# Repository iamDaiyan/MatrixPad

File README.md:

# MatrixPad
A 9 Key Programmable Macropad with Encoder & OLED Display<br><br>
MatrixPad is a fully programmable 9-key macropad designed for productivity, content creation, coding, and everyday shortcuts. Built around the **Seeed XIAO RP2040**, it features 9 Mechanical keys, a clean 3D-printed enclosure, rotary encoder input, and OLED display support.
## Features
* 9 Mechanical Keys (3x3 grid layout)
* Rotary Encoder 
* 0.91 inch OLED Display 
* Powered by Seeed XIAO RP2040 (Through-Hole)
* 2-Layer PCB (≤100mm x 100mm)
* Fully 3D Printed Case
* Programmable Firmware (KMK / QMK compatible)

---

## Overall Hackpad

## Schematic

## PCB

## Case Design

---

## BOM

| Item                          | Quantity |
|-------------------------------|----------|
| Seeed XIAO RP2040 (Through-Hole) | 1        |
| MX-Style Mechanical Switches  | 9        |
| Through-hole 1N4148 Diodes    | 9        |
| Blank DSA Keycaps (1u)        | 9        |
| SK6812 MINI-E LEDs             | 9        |
| EC11 Rotary Encoder            | 1        |
| 0.91” OLED (I2C)              | 1        |
| M3×16 mm Screws                | 4        |
| M3×5 mm Heatset Inserts        | 4        |
| PCB (2-Layer)                  | 1        |
| 3D Printed Case                | 1        |

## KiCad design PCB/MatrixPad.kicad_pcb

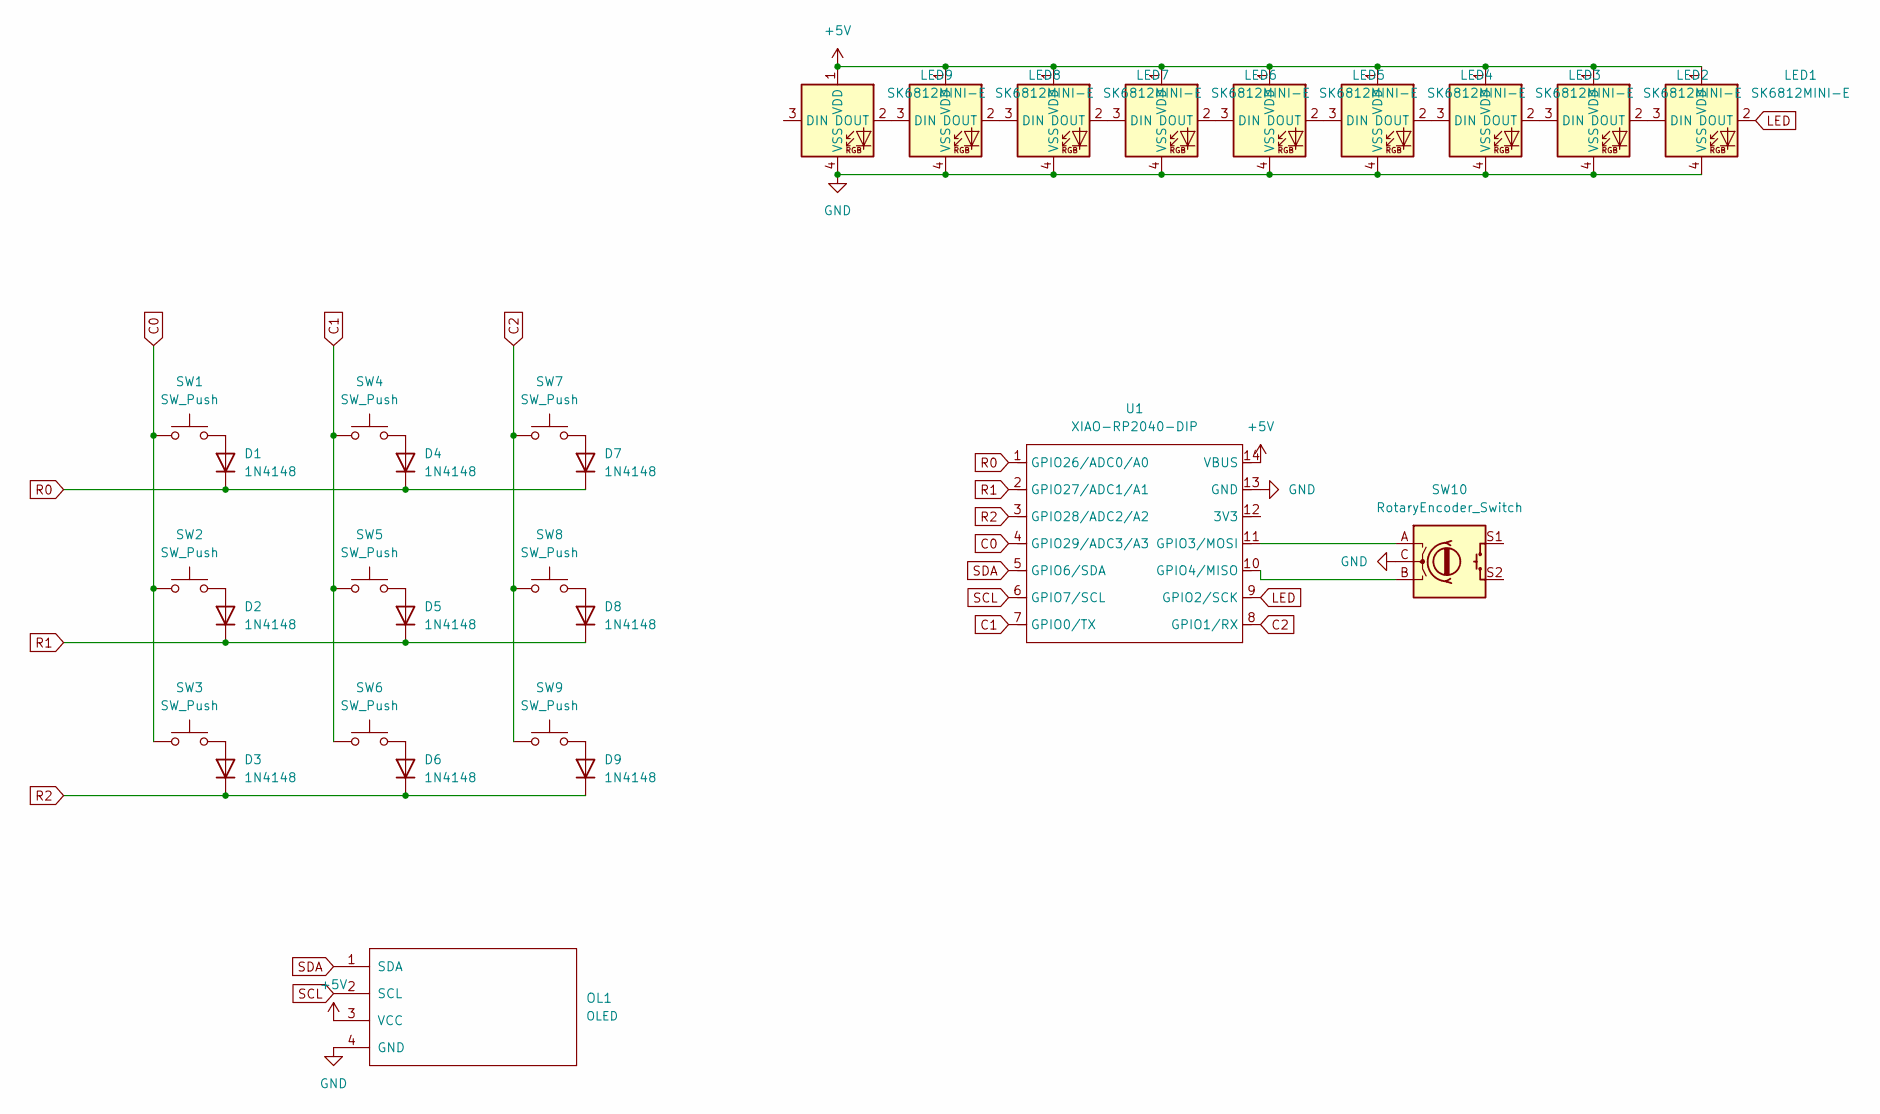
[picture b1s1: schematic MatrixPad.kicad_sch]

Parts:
D1, D2, D3, D4, D5, D6, D7, D8, D9: 1N4148; D_DO-35_SOD27_P7.62mm_Horizontal
LED1, LED2, LED3, LED4, LED5, LED6, LED7, LED8, LED9: SK6812MINI-E; LED_6028R
OL1: OLED; Adafruit_SSD1306
SW1, SW2, SW3, SW4, SW5, SW6, SW7, SW8, SW9: SW_Push; SW_Cherry_MX_1.00u_PCB
SW10: RotaryEncoder_Switch; RotaryEncoder_Alps_EC11E-Switch_Vertical_H20mm
U1: XIAO-RP2040-DIP

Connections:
+5V: LED1.1 (VDD), LED2.1 (VDD), LED3.1 (VDD), LED4.1 (VDD), LED5.1 (VDD), LED6.1 (VDD), LED7.1 (VDD), LED8.1 (VDD), LED9.1 (VDD), OL1.3 (VCC), U1.14 (VBUS)
C0: SW1.1, SW2.1, SW3.1, U1.4 (GPIO29/ADC3/A3)
C1: SW4.1, SW5.1, SW6.1, U1.7 (GPIO0/TX)
C2: SW7.1, SW8.1, SW9.1, U1.8 (GPIO1/RX)
GND: LED1.4 (VSS), LED2.4 (VSS), LED3.4 (VSS), LED4.4 (VSS), LED5.4 (VSS), LED6.4 (VSS), LED7.4 (VSS), LED8.4 (VSS), LED9.4 (VSS), OL1.4 (GND), SW10.C, U1.13 (GND)
LED: LED1.2 (DOUT), U1.9 (GPIO2/SCK)
unnamed: D1.2 (A), SW1.2
unnamed: D2.2 (A), SW2.2
unnamed: D3.2 (A), SW3.2
unnamed: D4.2 (A), SW4.2
unnamed: D5.2 (A), SW5.2
unnamed: D6.2 (A), SW6.2
unnamed: D7.2 (A), SW7.2
unnamed: D8.2 (A), SW8.2
unnamed: D9.2 (A), SW9.2
unnamed: LED1.3 (DIN), LED2.2 (DOUT)
unnamed: LED2.3 (DIN), LED3.2 (DOUT)
unnamed: LED3.3 (DIN), LED4.2 (DOUT)
unnamed: LED4.3 (DIN), LED5.2 (DOUT)
unnamed: LED5.3 (DIN), LED6.2 (DOUT)
unnamed: LED6.3 (DIN), LED7.2 (DOUT)
unnamed: LED7.3 (DIN), LED8.2 (DOUT)
unnamed: LED8.3 (DIN), LED9.2 (DOUT)
unnamed: SW10.A, U1.11 (GPIO3/MOSI)
unnamed: SW10.B, U1.10 (GPIO4/MISO)
R0: D1.1 (K), D4.1 (K), D7.1 (K), U1.1 (GPIO26/ADC0/A0)
R1: D2.1 (K), D5.1 (K), D8.1 (K), U1.2 (GPIO27/ADC1/A1)
R2: D3.1 (K), D6.1 (K), D9.1 (K), U1.3 (GPIO28/ADC2/A2)
SCL: OL1.2 (SCL), U1.6 (GPIO7/SCL)
SDA: OL1.1 (SDA), U1.5 (GPIO6/SDA)

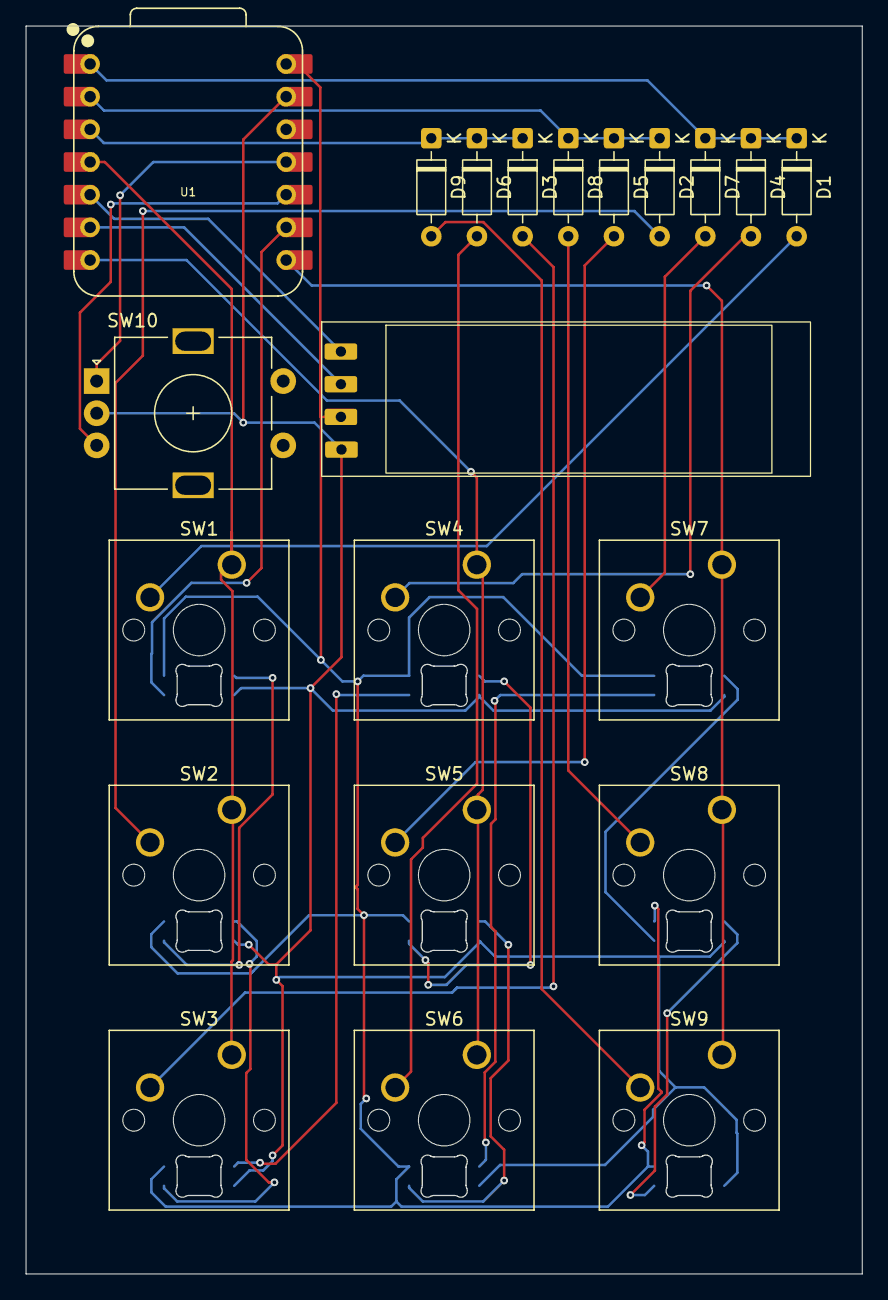
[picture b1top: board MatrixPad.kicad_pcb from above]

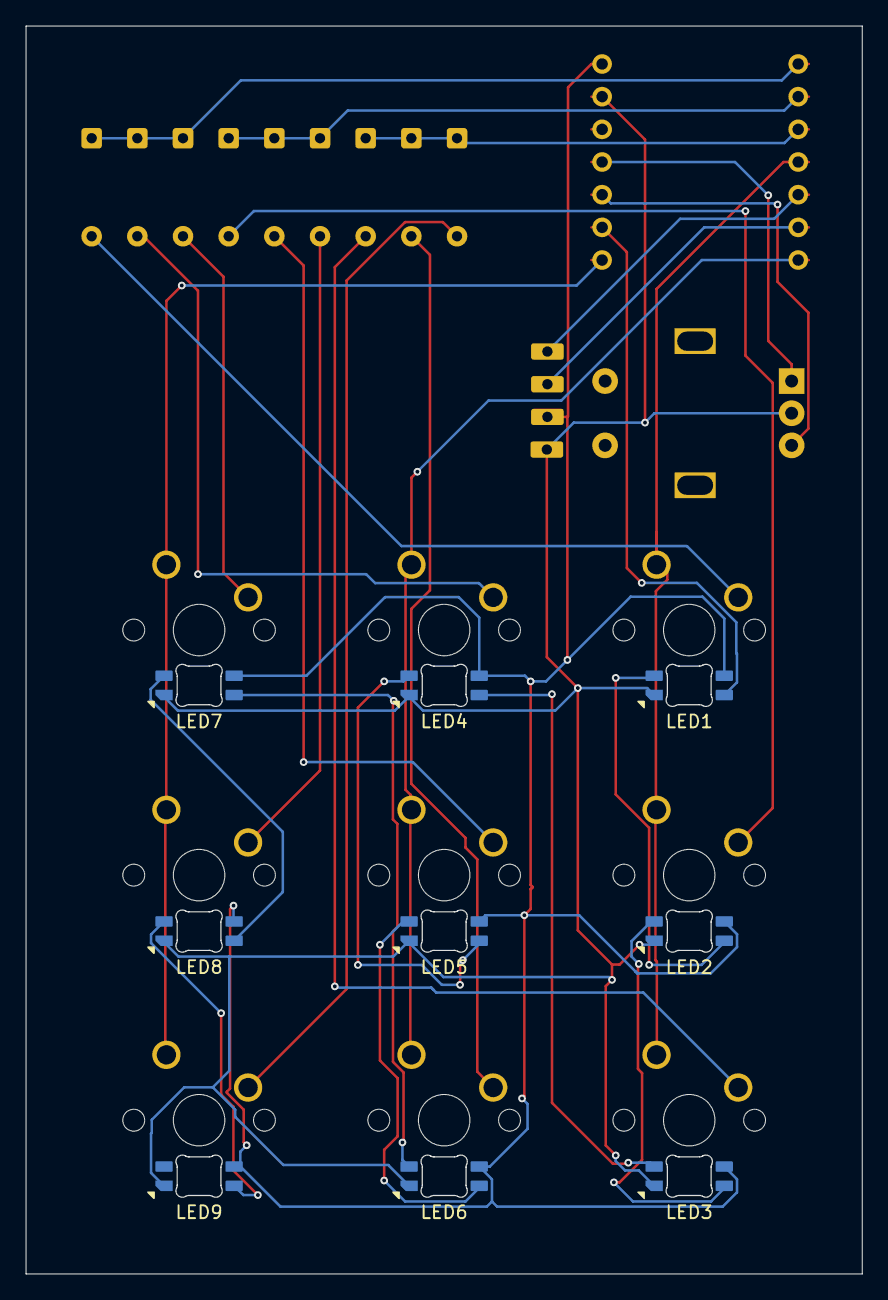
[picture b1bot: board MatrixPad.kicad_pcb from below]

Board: 2 copper layers, 64.9 x 97.0 mm, 30 parts (9 on the bottom side), 30 nets.

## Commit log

2026-02-12 Added MatrixPad project files
2026-02-12 Added some more project files
2026-02-13 Added images, firmware, and updated Gerber files
2026-02-13 Rename images to remove spaces
2026-02-13 Copied code.py to Production from Firmware
2026-02-13 Added the USB-C cutout
